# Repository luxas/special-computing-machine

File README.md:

# special-computing-machine
Let's make a Raspberry Pi cluster similar to real data centers!

# 3D models
The 3D model files in [hardware/models](hardware/models) include the following models by external authors, licensed for non-commercial use from [GrabCAD](https://grabcad.com).

 - [Raspberry Pi 4 Model B](https://grabcad.com/library/raspberry-pi-4-model-b-1) by [Hasanain Shuja](https://grabcad.com/hasanain.shuja-1)
 - [Intel 2.5" SSD 520 Series](https://grabcad.com/library/intel-2-5-ssd-520-series-1) by [Kevin Yu](https://grabcad.com/kevin.yu-7)

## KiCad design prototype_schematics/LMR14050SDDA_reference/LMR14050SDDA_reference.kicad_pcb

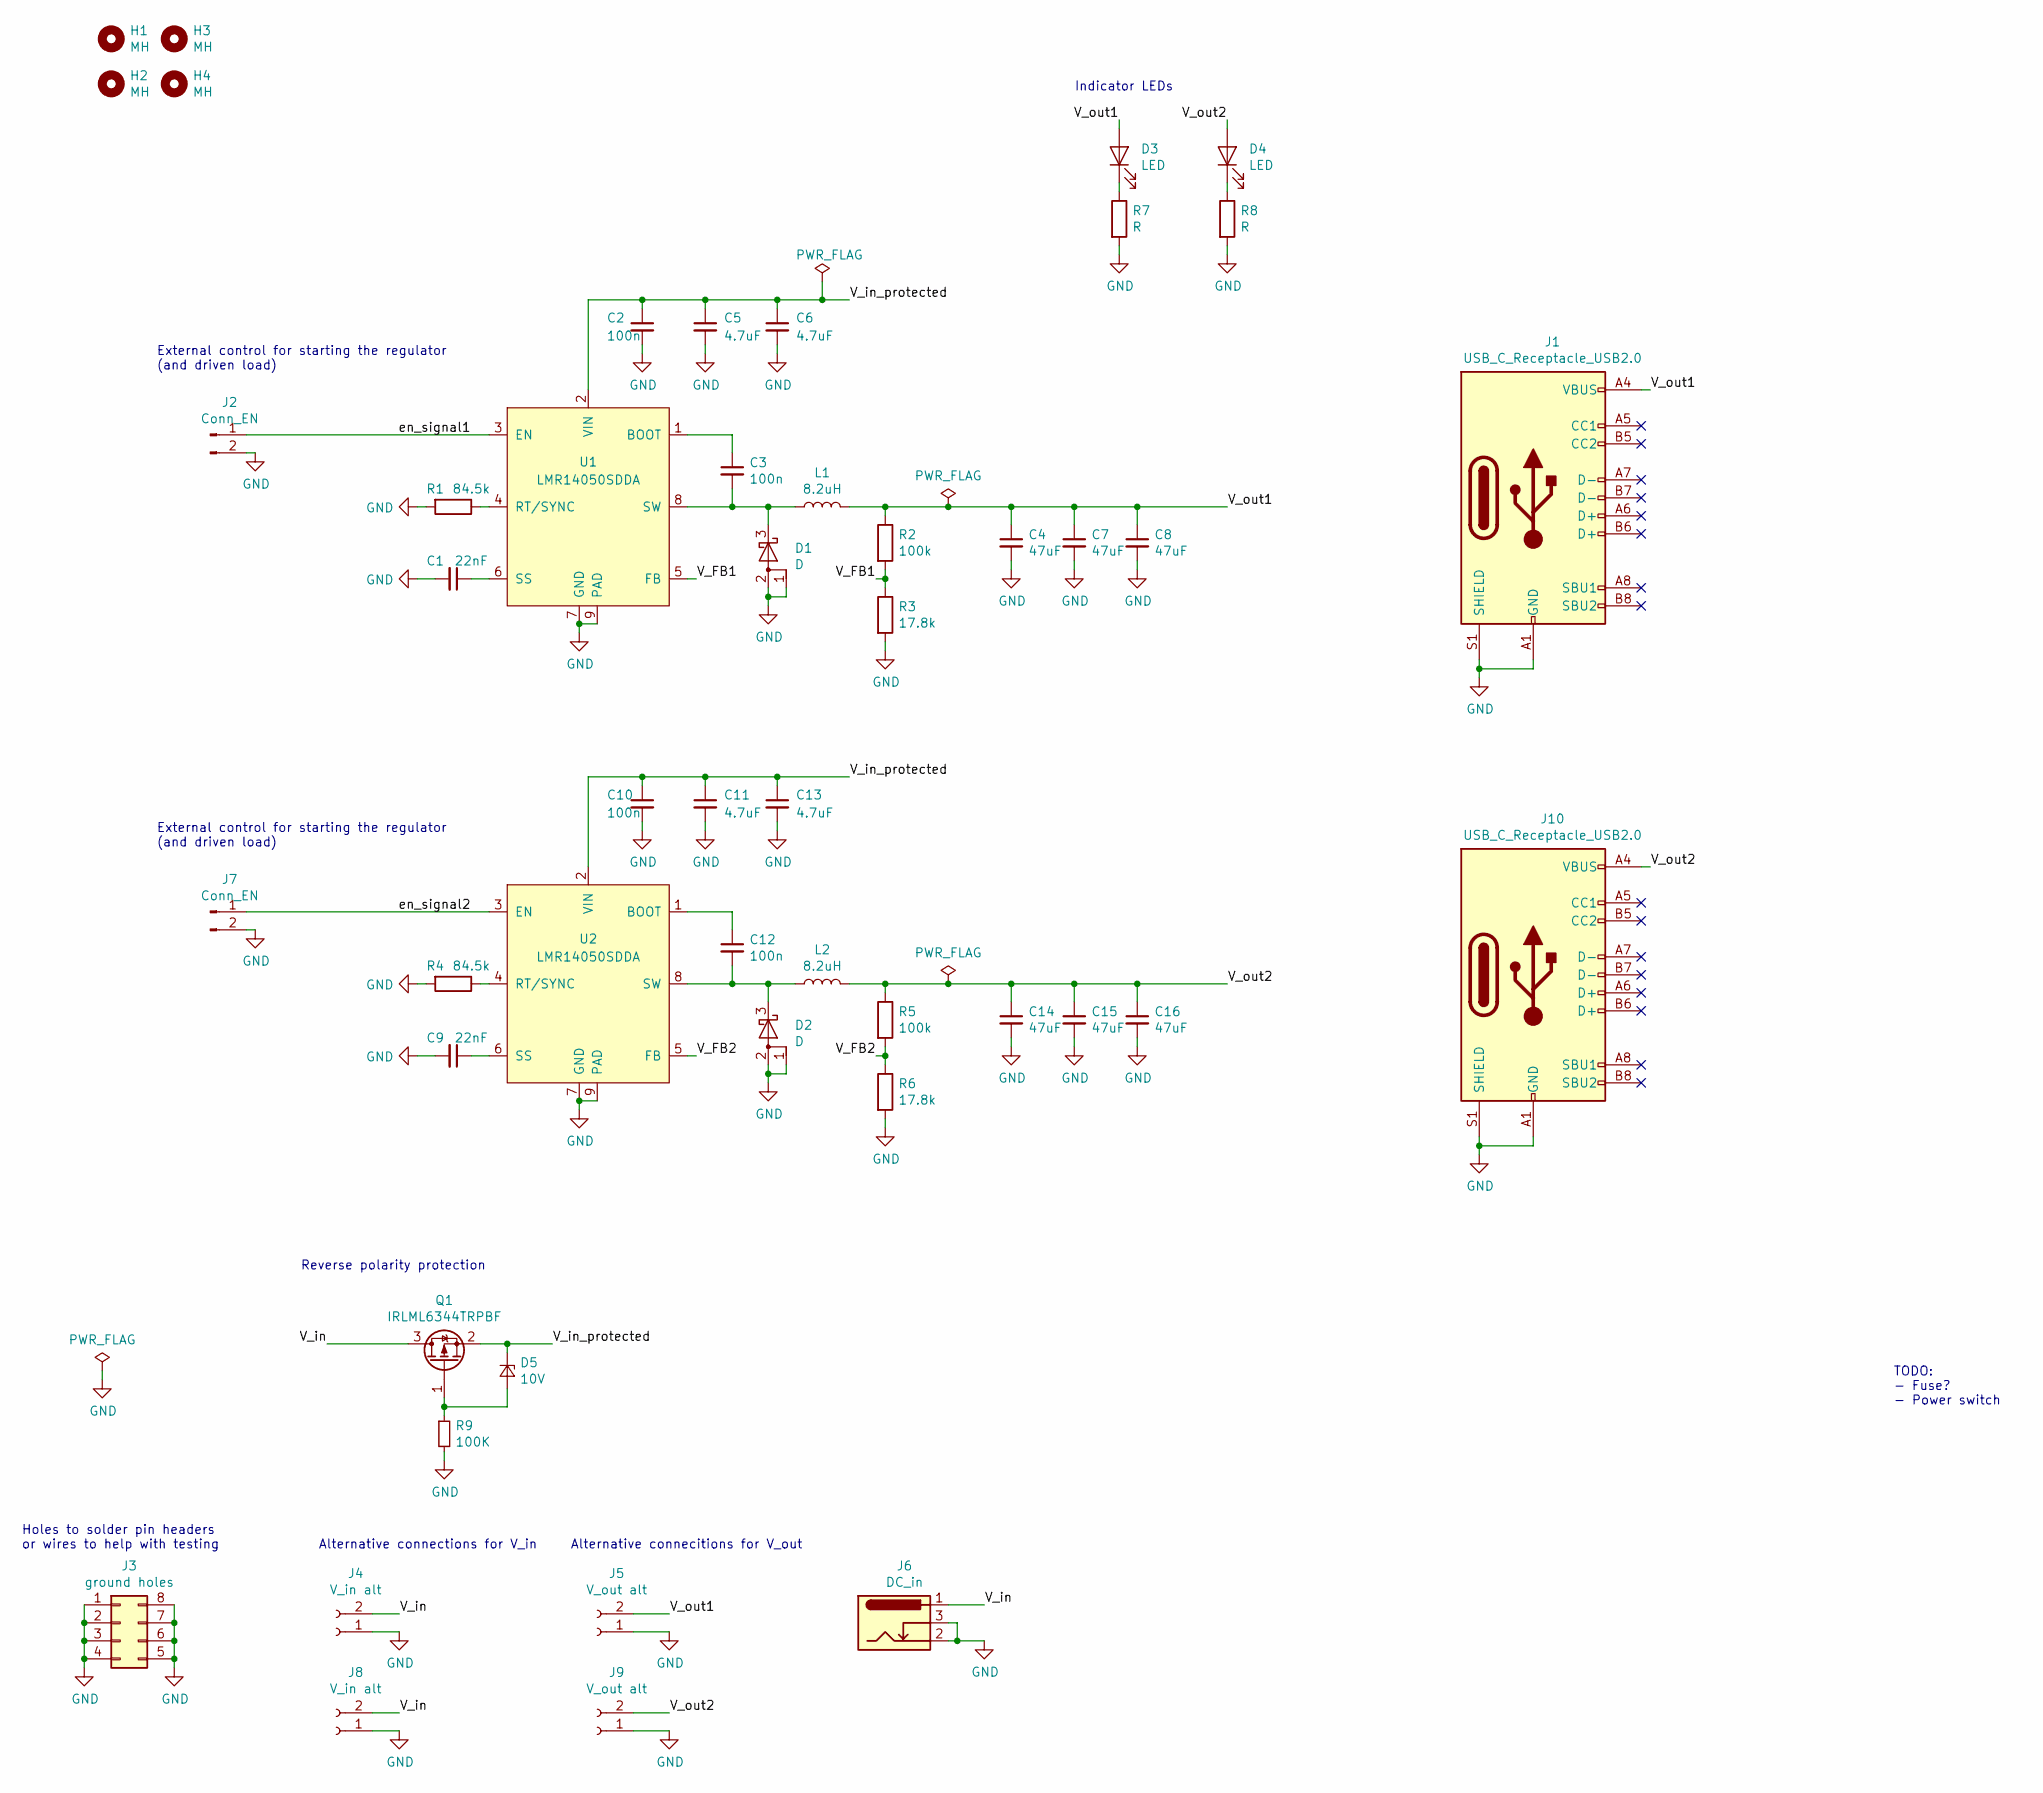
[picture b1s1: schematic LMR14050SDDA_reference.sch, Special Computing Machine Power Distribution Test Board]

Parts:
C1, C9: 22nF; C_0603_1608Metric
C2, C3, C10, C12: 100n; C_0603_1608Metric
C4, C7, C8, C14, C15, C16: 47uF; C_1210_3225Metric
C5, C6, C11, C13: 4.7uF; C_1206_3216Metric
D1, D2: D; TO-277A
D3, D4: LED; LED_0805_2012Metric
D5: 10V; D_SOD-323
H1, H2, H3, H4: MH; MountingHole_3.2mm_M3
J1, J10: USB_C_Receptacle_USB2.0; USB_C_Receptacle_GCT_USB4085
J2, J7: Conn_EN; PinHeader_1x02_P2.54mm_Vertical
J3: ground holes; PinHeader_2x04_P2.54mm_Vertical
J4, J8: V_in alt; TerminalBlock_bornier-2_P5.08mm
J5, J9: V_out alt; TerminalBlock_bornier-2_P5.08mm
J6: DC_in; BarrelJack_Wuerth_6941xx301002
L1, L2: 8.2uH; L_Wuerth_WE-PD-Typ-LS
Q1: IRLML6344TRPBF; SOT-23
R1, R4: 84.5k; R_0603_1608Metric
R2, R5: 100k; R_0603_1608Metric
R3, R6: 17.8k; R_0603_1608Metric
R7, R8: R; R_0805_2012Metric
R9: 100K; R_0603_1608Metric
U1, U2: LMR14050SDDA; Texas_HSOP-8-1EP_3.9x4.9mm_P1.27mm_ThermalVias

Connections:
/V_FB1: R2.2, R3.1, U1.5 (FB)
/V_FB2: R5.2, R6.1, U2.5 (FB)
/V_in: J4.2, J6.1, J8.2, Q1.3 (D)
/V_in_protected: C2.1, C5.1, C6.1, C10.1, C11.1, C13.1, D5.1 (K), Q1.2 (S), U1.2 (VIN), U2.2 (VIN)
/V_out1: C4.1, C7.1, C8.1, D3.2 (A), J1.A4 (VBUS), J1.A9 (VBUS), J1.B4 (VBUS), J1.B9 (VBUS), J5.2, L1.2, R2.1
/V_out2: C14.1, C15.1, C16.1, D4.2 (A), J9.2, J10.A4 (VBUS), J10.A9 (VBUS), J10.B4 (VBUS), J10.B9 (VBUS), L2.2, R5.1
/en_signal1: J2.1, U1.3 (EN)
/en_signal2: J7.1, U2.3 (EN)
GND: C1.2, C2.2, C4.2, C5.2, C6.2, C7.2, C8.2, C9.2, C10.2, C11.2, C13.2, C14.2, C15.2, C16.2, D1.1 (A), D1.2 (A), D2.1 (A), D2.2 (A), J1.A1 (GND), J1.A12 (GND), J1.B1 (GND), J1.B12 (GND), J1.S1 (SHIELD), J2.2, J3.1, J3.2, J3.3, J3.4, J3.5, J3.6, J3.7, J3.8, J4.1, J5.1, J6.2, J6.3, J7.2, J8.1, J9.1, J10.A1 (GND), J10.A12 (GND), J10.B1 (GND), J10.B12 (GND), J10.S1 (SHIELD), R1.2, R3.2, R4.2, R6.2, R7.2, R8.2, R9.2, U1.7 (GND), U1.9 (PAD), U2.7 (GND), U2.9 (PAD)
unnamed: C1.1, U1.6 (SS)
unnamed: C3.1, U1.1 (BOOT)
unnamed: C3.2, D1.3 (K), L1.1, U1.8 (SW)
unnamed: C9.1, U2.6 (SS)
unnamed: C12.1, U2.1 (BOOT)
unnamed: C12.2, D2.3 (K), L2.1, U2.8 (SW)
unnamed: D3.1 (K), R7.1
unnamed: D4.1 (K), R8.1
unnamed: D5.2 (A), Q1.1 (G), R9.1
unnamed: R1.1, U1.4 (RT/SYNC)
unnamed: R4.1, U2.4 (RT/SYNC)

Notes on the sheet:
External control for starting the regulator (and driven load)
Holes to solder pin headers or wires to help with testing
Alternative connections for V_in
Alternative connecitions for V_out
TODO: - Fuse? - Power switch
Indicator LEDs
Reverse polarity protection

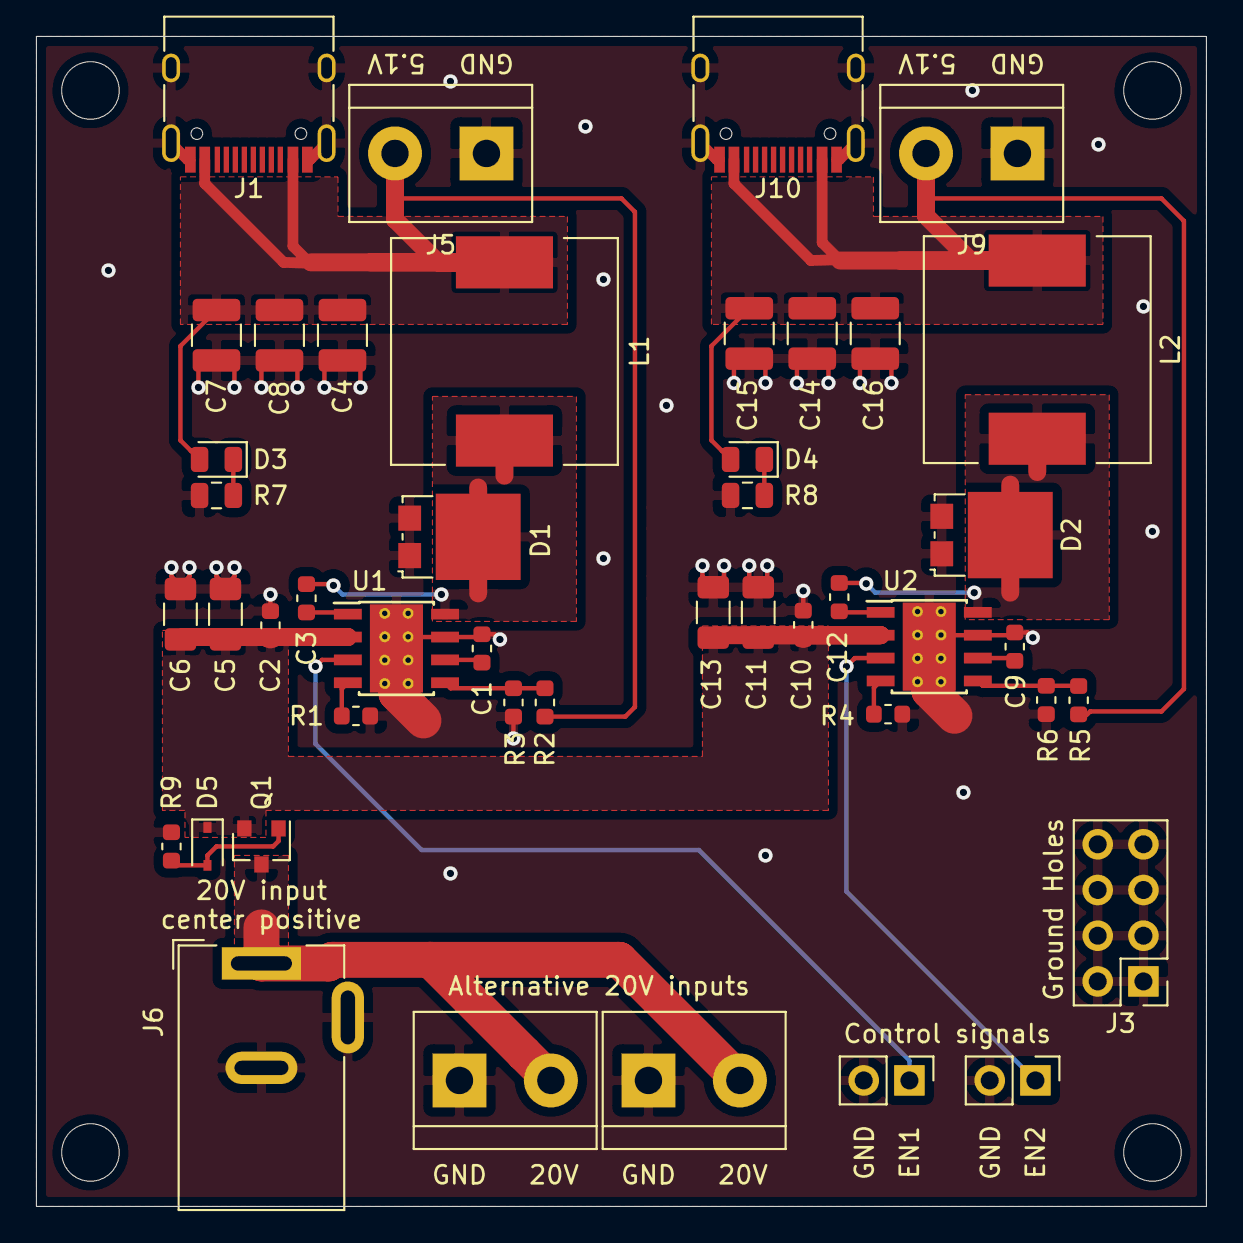
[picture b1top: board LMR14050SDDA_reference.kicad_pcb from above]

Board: 2 copper layers, 65.0 x 65.0 mm, 49 parts (0 on the bottom side), 20 nets.

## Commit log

2020-03-12 Add iperf python script.
2020-03-12 Implement UDP, and refactor the script
2020-03-12 Add iperf wrapper script
2020-03-17 Remove unnecessary line from iperf.py
    There was one deprecated fixup in here.
2020-04-18 WIP add work in progress buck converter schematic
2020-04-22 WIP Add power distribution test board rev 1.
2020-04-22 Add schematic information.
2020-04-24 Final changes for ordering.
2020-04-24 Change USB C receptacle to a component that's in stock.
2020-05-02 2 tabs design
2020-05-04 WebUI
2020-05-04 Added and removed buttons
2020-05-05 testing git commit
2020-05-05 commit changes
2020-05-05 THis is just a fucking test
2020-05-05 message for commit
2020-05-05 a meaningless change
2020-05-05 Add some new content and change the color of a few elements
2020-05-05 Initial commit system-api: empty cmd dirs
2020-05-05 Add one fake "SPI" implementation over PTY UART/serial
2020-05-05 Add project meta-files
2020-05-07 Somewhat interative.
2020-05-08 Add interactive to the website
2020-05-09 Add interactive button. The button does not send proper request yet.
2020-05-13 Made changes to harbor the change in the object. Reflection of change into the UI needs to be figured out
2020-05-15 The button functionality is working finally.
2020-05-15 added/removed
2020-05-15 Fully interactive on Compute tab.
2020-05-20 Add some information on Cluster tab.
2020-05-20 Forgot to change GHz to W
2020-05-27 Check in initial types
2020-05-27 Add sample demo page for interactive HTML for inspiration for the web UI
2020-05-27 Add some tuf hacks/tests
2020-05-27 Add the STEP file for the compute unit tray design
2020-05-27 Relicense future work under Apache 2.0
2020-05-27 Add Phoronix files
2020-05-27 Add (not working) setup script for running Phoronix on a Pi
2020-05-27 Move place of the PSU source code
2020-05-27 remove unnecessary file
2020-05-27 Credit model authors in README
2020-07-17 Fix external control header silkscreen labels.
2021-02-21 test.drawio
